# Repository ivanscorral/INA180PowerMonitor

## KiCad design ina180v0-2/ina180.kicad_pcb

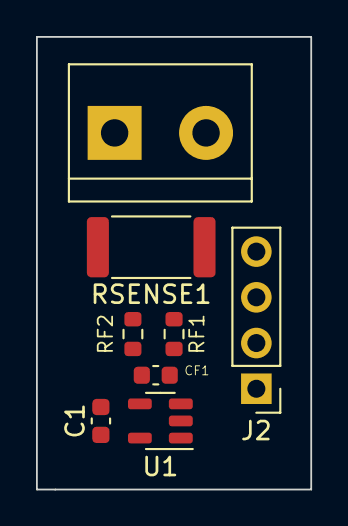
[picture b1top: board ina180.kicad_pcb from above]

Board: 2 copper layers, 15.2 x 25.1 mm, 8 parts (0 on the bottom side), 7 nets, no tracks yet.

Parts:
C1: 100n; C_0603_1608Metric
CF1: 8n; C_0603_1608Metric
J1: VIN; TerminalBlock_bornier-2_P5.08mm
J2: IO; PinHeader_1x04_P2.54mm_Vertical
RF1, RF2: 10R; R_0603_1608Metric
RSENSE1: R005; R_2512_6332Metric
U1: INA180A2; SOT-23-5

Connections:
/IN+: J1.2, RF1.2, RSENSE1.1
/IN-: J1.1, RF2.2, RSENSE1.2
/VIN+: CF1.1, RF1.1, U1.3 (+)
/VIN-: CF1.2, RF2.1, U1.4 (-)
/VOUT: J2.2, J2.3, U1.1
GND: C1.2, J2.4, U1.2 (GND)
VCC: C1.1, J2.1, U1.5 (V+)

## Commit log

2022-12-21 Revamped project structure
2022-12-21 Renamed root directory
2022-12-21 Removed old files
2022-12-31 Improved schematic
2023-01-04 Added power flags and changed to nets
2023-01-04 Removed comment and adjusted schematic borders
2023-01-04 Adjusted capacitor values
2023-01-04 Fixed schematic and added first pcb preview
2023-01-04 Added footprints for terminal, and updated schematic
